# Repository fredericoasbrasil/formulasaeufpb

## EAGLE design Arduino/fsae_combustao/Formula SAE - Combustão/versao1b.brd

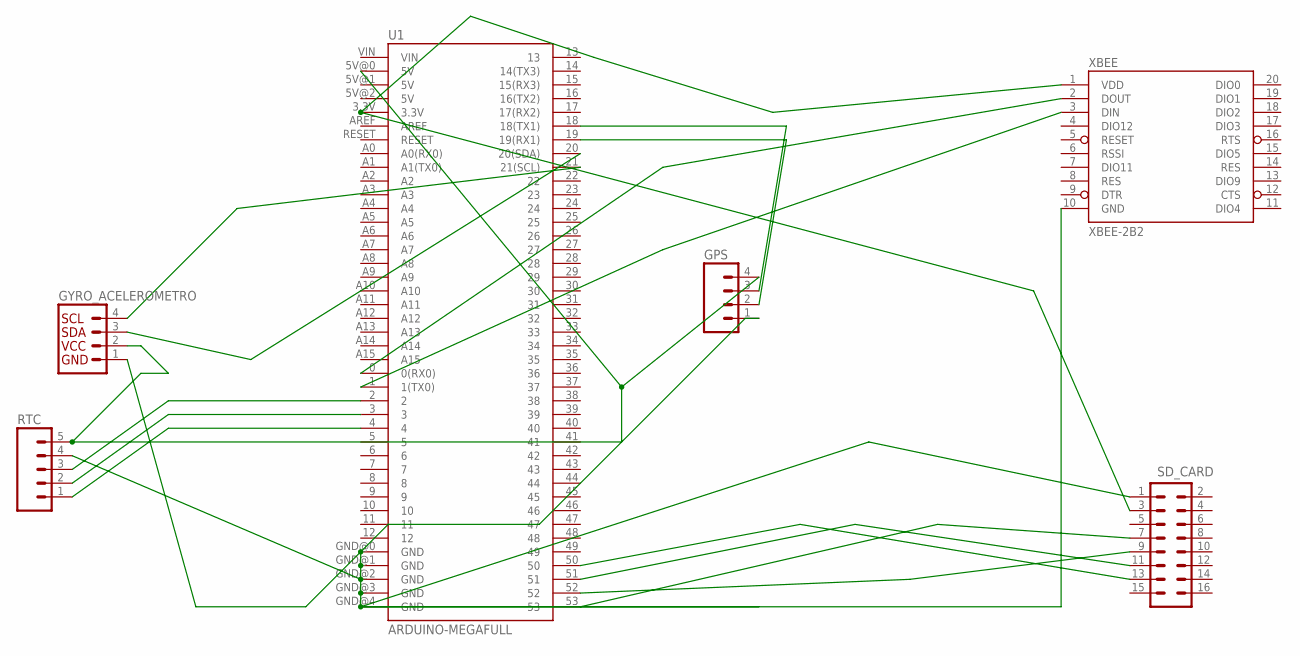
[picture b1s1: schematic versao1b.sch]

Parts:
GPS: M04LOCK; 1X04_LOCK
GYRO_ACELEROMETRO: I2C_STANDARD; 1X04
RTC: M05LOCK; 1X05_LOCK
SD_CARD: M08X2; 2X8
U1: ARDUINO-MEGAFULL; ARDUINO_MEGA
XBEE: XBEE-2B2; XBEE-SILK

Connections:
GND: GPS.1, GYRO_ACELEROMETRO.1, RTC.4, SD_CARD.1, U1.GND@0 (GND), U1.GND@1 (GND), U1.GND@2 (GND), U1.GND@3 (GND), U1.GND@4 (GND), XBEE.10 (GND)
unnamed: GPS.4, GYRO_ACELEROMETRO.2, RTC.5, U1.5V@0 (5V)
unnamed: RTC.3, U1.2
unnamed: U1.0 (0(RX0)), XBEE.2 (DOUT)
unnamed: U1.1 (1(TX0)), XBEE.3 (DIN)
unnamed: SD_CARD.3, U1.3.3V, XBEE.1 (VDD)
unnamed: GPS.3, U1.18 (18(TX1))
unnamed: GPS.2, U1.19 (19(RX1))
unnamed: RTC.2, U1.3
unnamed: RTC.1, U1.4
unnamed: GYRO_ACELEROMETRO.3, U1.20 (20(SDA))
unnamed: GYRO_ACELEROMETRO.4, U1.21 (21(SCL))
unnamed: SD_CARD.13, U1.50
unnamed: SD_CARD.11, U1.51
unnamed: SD_CARD.9, U1.52
unnamed: SD_CARD.7, U1.53

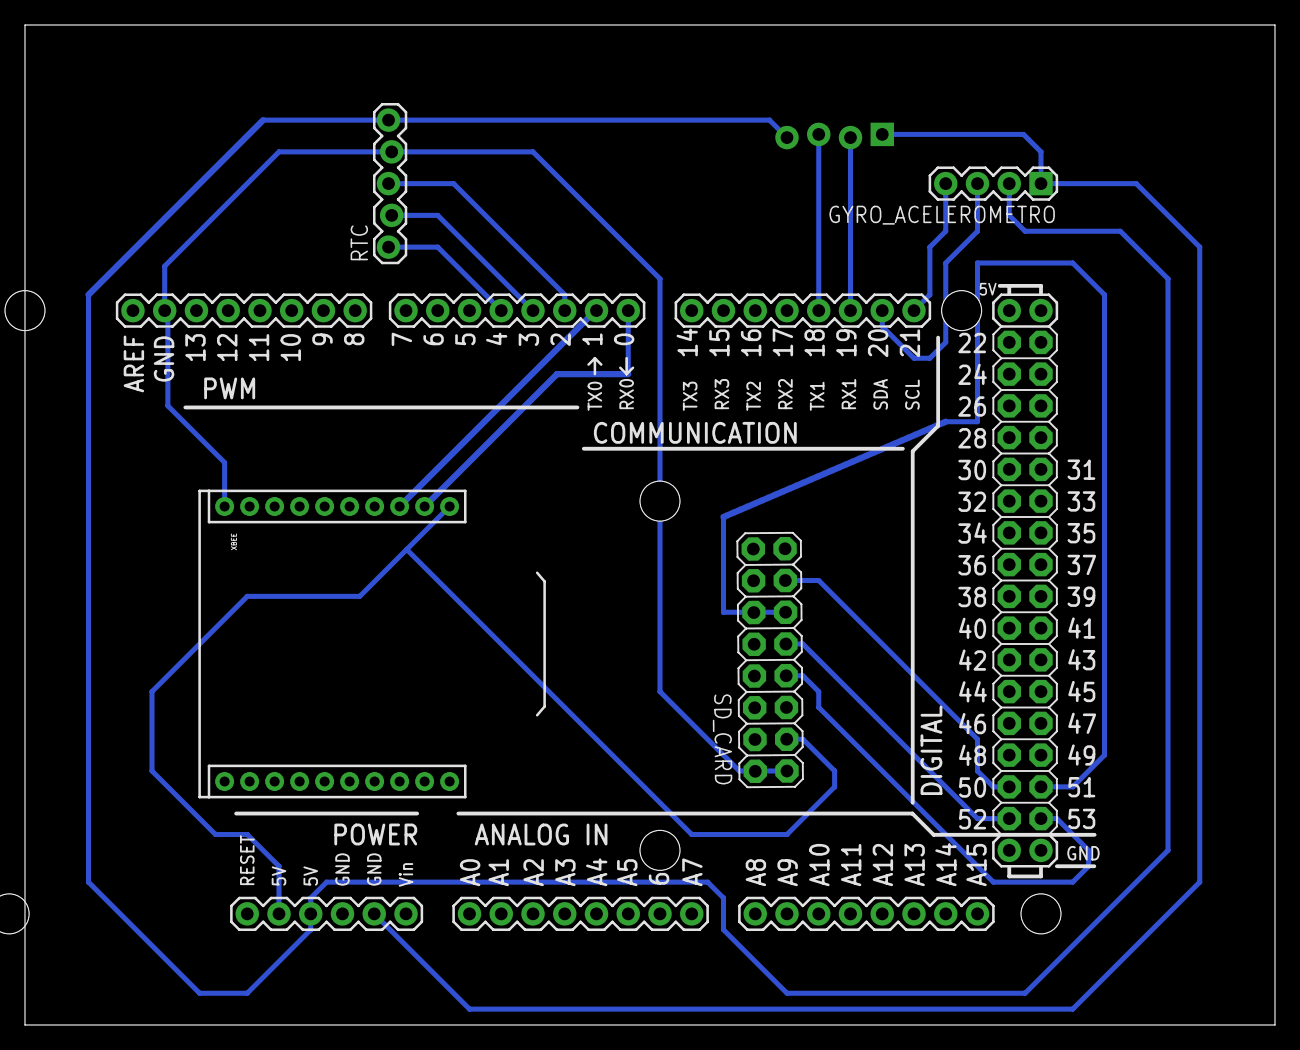
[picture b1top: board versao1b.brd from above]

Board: 2 copper layers, 100.0 x 80.0 mm, 6 parts (1 on the bottom side), 16 nets.

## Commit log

2015-07-28 Commit de teste
    apenas teste, descartar
2015-07-28 Protoboard inicial
2015-07-29 mensagem teste para o tutorial
2015-07-29 mensagem teste commit
2015-07-29 Diagrama inicial de classes - Criado com o DIA
2015-08-02 Apenas teste de upload
2015-08-03 Inkscape adesivo
2015-08-04 Versão inicial do Giroscopio
    Teste github
2015-08-13 Modificação no arquivo GPS
    Envio de Datasheet e Alterações de teste no giroscópio
2015-08-14 Angulo e Aceleração por Giroscópio GY 80
    Programas de aquisição de dados para Arduíno, um recebe a aceleração e
    outro o angulo
2015-08-25 gps-fsae-v2.ino
    Imprime: DATA,HORA,VELOCIDADE,LATITUDE,LONGITUDE,ALTITUDE,SATELITES
2015-09-03 GPS no Arduino MEga 2560 (Hardware Serial)
2015-09-03 Sensoriamento_Formula_Combustão_UFPB 1.0
    Aquisição de dados do GPS, GY 80 e dados em SD, transmissão XBEE
2015-09-04 Fritzing Combustão e Imagens Pinout Mega 2560
2015-09-08 Combustão 2015
    Versão Final do que será embarcado no carro a combustão para a
    competição de 2015.
2015-09-08 GPS Ok
2015-09-13 Bibliotecas e teste RTC
2015-09-15 Banner e Eagle
2015-09-16 Organização e RTC
2015-09-17 Correção do GPS
2015-09-20 Create Processing
2015-09-20 Programa teste do gyro
2015-09-23 Atualização 21092015
2015-09-25 18:00 25/09
2015-10-01 01/10
2015-11-05 5.11
2015-11-07 07.11
2015-11-19 ATUALIZAÇÃO DO REPOSITORIO

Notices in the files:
parts and their libraries:
SparkFun-Connectors: Licensing: Creative Commons ShareAlike 4.0 International - https://creativecommons.org/licenses/by-sa/4.0
